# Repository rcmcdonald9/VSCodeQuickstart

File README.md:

# Pip: a 3D-printed AI robot dog, designed to be easy to assemble

A small four-legged robot dog (about 25 cm long, ~1.9 kg) that you print on a **Bambu Lab P2S** and run on a **Raspberry Pi 5**.

- **Moving head:** pans and tilts, with a camera, distance sensor, speaker and mic.
- **Voice:** listens for commands offline and talks back.
- **AI:** hands harder requests to **Claude**, which plans multi-step tasks with the dog's tools and camera.

**v2 is designed so that every step is a straight-down move**, with one screw type and automatic calibration. A person with a screwdriver assembles it quickly, and a cheap machine could do it later. Every change is checked in a **physics simulation** before printing.

## What's here

| Path | What |
|---|---|
| [`cad/`](cad) | Parametric OpenSCAD design: `params.scad`, `lib.scad`, `assembly.scad`. [`cad/stl/`](cad/stl) has print-ready STLs (no supports, no inserts) plus the leg jig. |
| [`software/`](software) | Python stack: kinematics, trot gait, bus-servo driver, head, vision, navigation, voice, Claude brain, calibration. 57 tests. |
| [`sim/`](sim) | MuJoCo simulation built from the CAD and driven by the real controller. Results and video in [`sim/results/`](sim/results). |
| [`docs/ASSEMBLY_FIRST_DESIGN.md`](docs/ASSEMBLY_FIRST_DESIGN.md) | Why it's built this way: precedent, design rules, the cheap assembly-tool ladder |
| [`docs/SIMULATION.md`](docs/SIMULATION.md) | What the sim found and what changed because of it |
| [`docs/BOM.md`](docs/BOM.md) · [`PRINTING.md`](docs/PRINTING.md) · [`WIRING.md`](docs/WIRING.md) · [`ASSEMBLY.md`](docs/ASSEMBLY.md) · [`SOFTWARE.md`](docs/SOFTWARE.md) | Build guides |

## How the design makes assembly easy

- **4 identical leg modules.** The left side uses the same module turned 180°. Each is built straight down in a printed jig, then drops into a tray socket.
- **Smart bus servos (Feetech STS3215).** They're daisy-chained, and their encoders give **automatic calibration**: the jig holds the leg straight, and one command records the zeros.
- **One standard servo cup and one cap** hold all 10 servos.
- **One fastener: M3 × 8.** No heat-set inserts.
- **Each part is held by the next one.** The deck traps the legs. The head drops onto a keyed hub.
- **Chamfered lead-ins** on every mating edge, and **grip lugs** with a datum notch on the main parts.

## Simulation highlights ([details](docs/SIMULATION.md))

Using the real control code against a model built from the CAD:

- Walks at **100–200 mm/s within 2 %** of the commanded speed, with **≤ 2° roll**.
- Turns in place at **45°/s**, backs up, holds every pose, and moves the head while walking. **No falls** in the 53 s test.
- Things the sim caught and fixed before any printing:
  - a wobbly gait
  - a robot that couldn't turn
  - a fall on a walking turn
  - a forward creep
  - a stop bug
  - a knee/tray collision limit
- **Warning:** the knee servos run close to their continuous torque rating while walking. Expect warm servos on long walks.

## The plan

1. **Order parts** ([BOM.md](docs/BOM.md)). The servos are half the cost. Buy the **12 V** STS3215.
2. **While you wait:** run the sim (`pip install -e "software[sim]" && python sim/run_sim.py --quick`) and the software (`python -m robodog --sim --local`).
3. **Print the test-fit pair** ([PRINTING.md §1](docs/PRINTING.md)), then the rest: about 27 h, two 1 kg spools of PETG.
4. **Set servo IDs, build the legs in the jig, calibrate, stack the body** ([ASSEMBLY.md](docs/ASSEMBLY.md)).
5. **First walk** with typed commands, then calibrate drift and turning on your floor, then turn on voice and Claude.

## Specs

| | |
|---|---|
| Degrees of freedom | 8 legs (hip pitch + knee) + 2 head (pan, tilt) |
| Actuators | 10 × Feetech STS3215 12 V bus servos (30 kg·cm stall) |
| Legs | 100 mm + 100 mm, 170 mm standing hip height |
| Compute | Raspberry Pi 5 (8 GB) |
| Sensors | Camera Module 3, VL53L1X time-of-flight (both in the head) |
| Voice | Vosk (offline speech-to-text) + Piper (offline text-to-speech), wake word "Hey Pip" |
| AI | Claude via the Anthropic API (tool use + vision), with an offline keyword fallback |
| Power | 3S2P Li-ion pack with BMS → servos directly, 5 V buck → Pi. Sim estimate: about 1–2 h. |

v1 (12 PWM servos with hip roll) is in the git history at commit `9178ef9`.

MIT licensed.

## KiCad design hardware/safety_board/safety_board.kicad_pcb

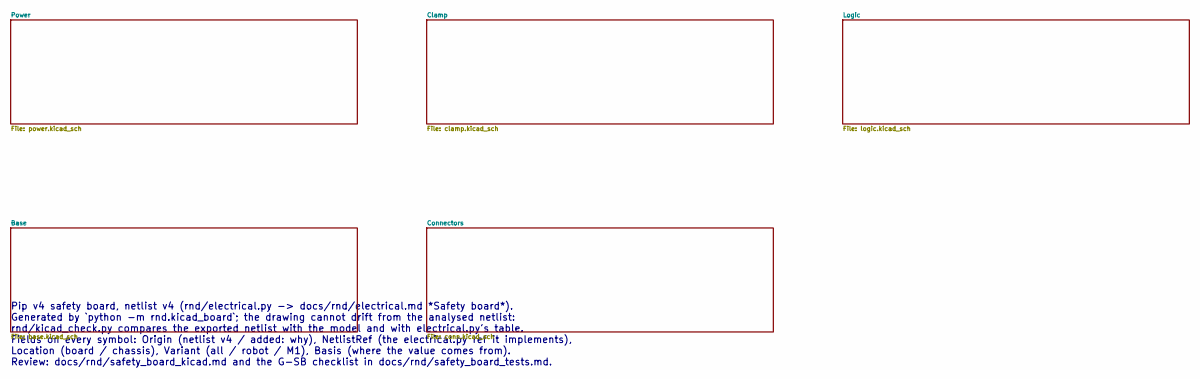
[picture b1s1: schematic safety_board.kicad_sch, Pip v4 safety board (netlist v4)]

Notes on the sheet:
Pip v4 safety board, netlist v4 (rnd/electrical.py -> docs/rnd/electrical.md *Safety board*). Generated by `python -m rnd.kicad_board`; the drawing cannot drift from the analysed netlist: rnd/kicad_check.py compares the exported netlist with the model and with electrical.py's table. Fields on every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

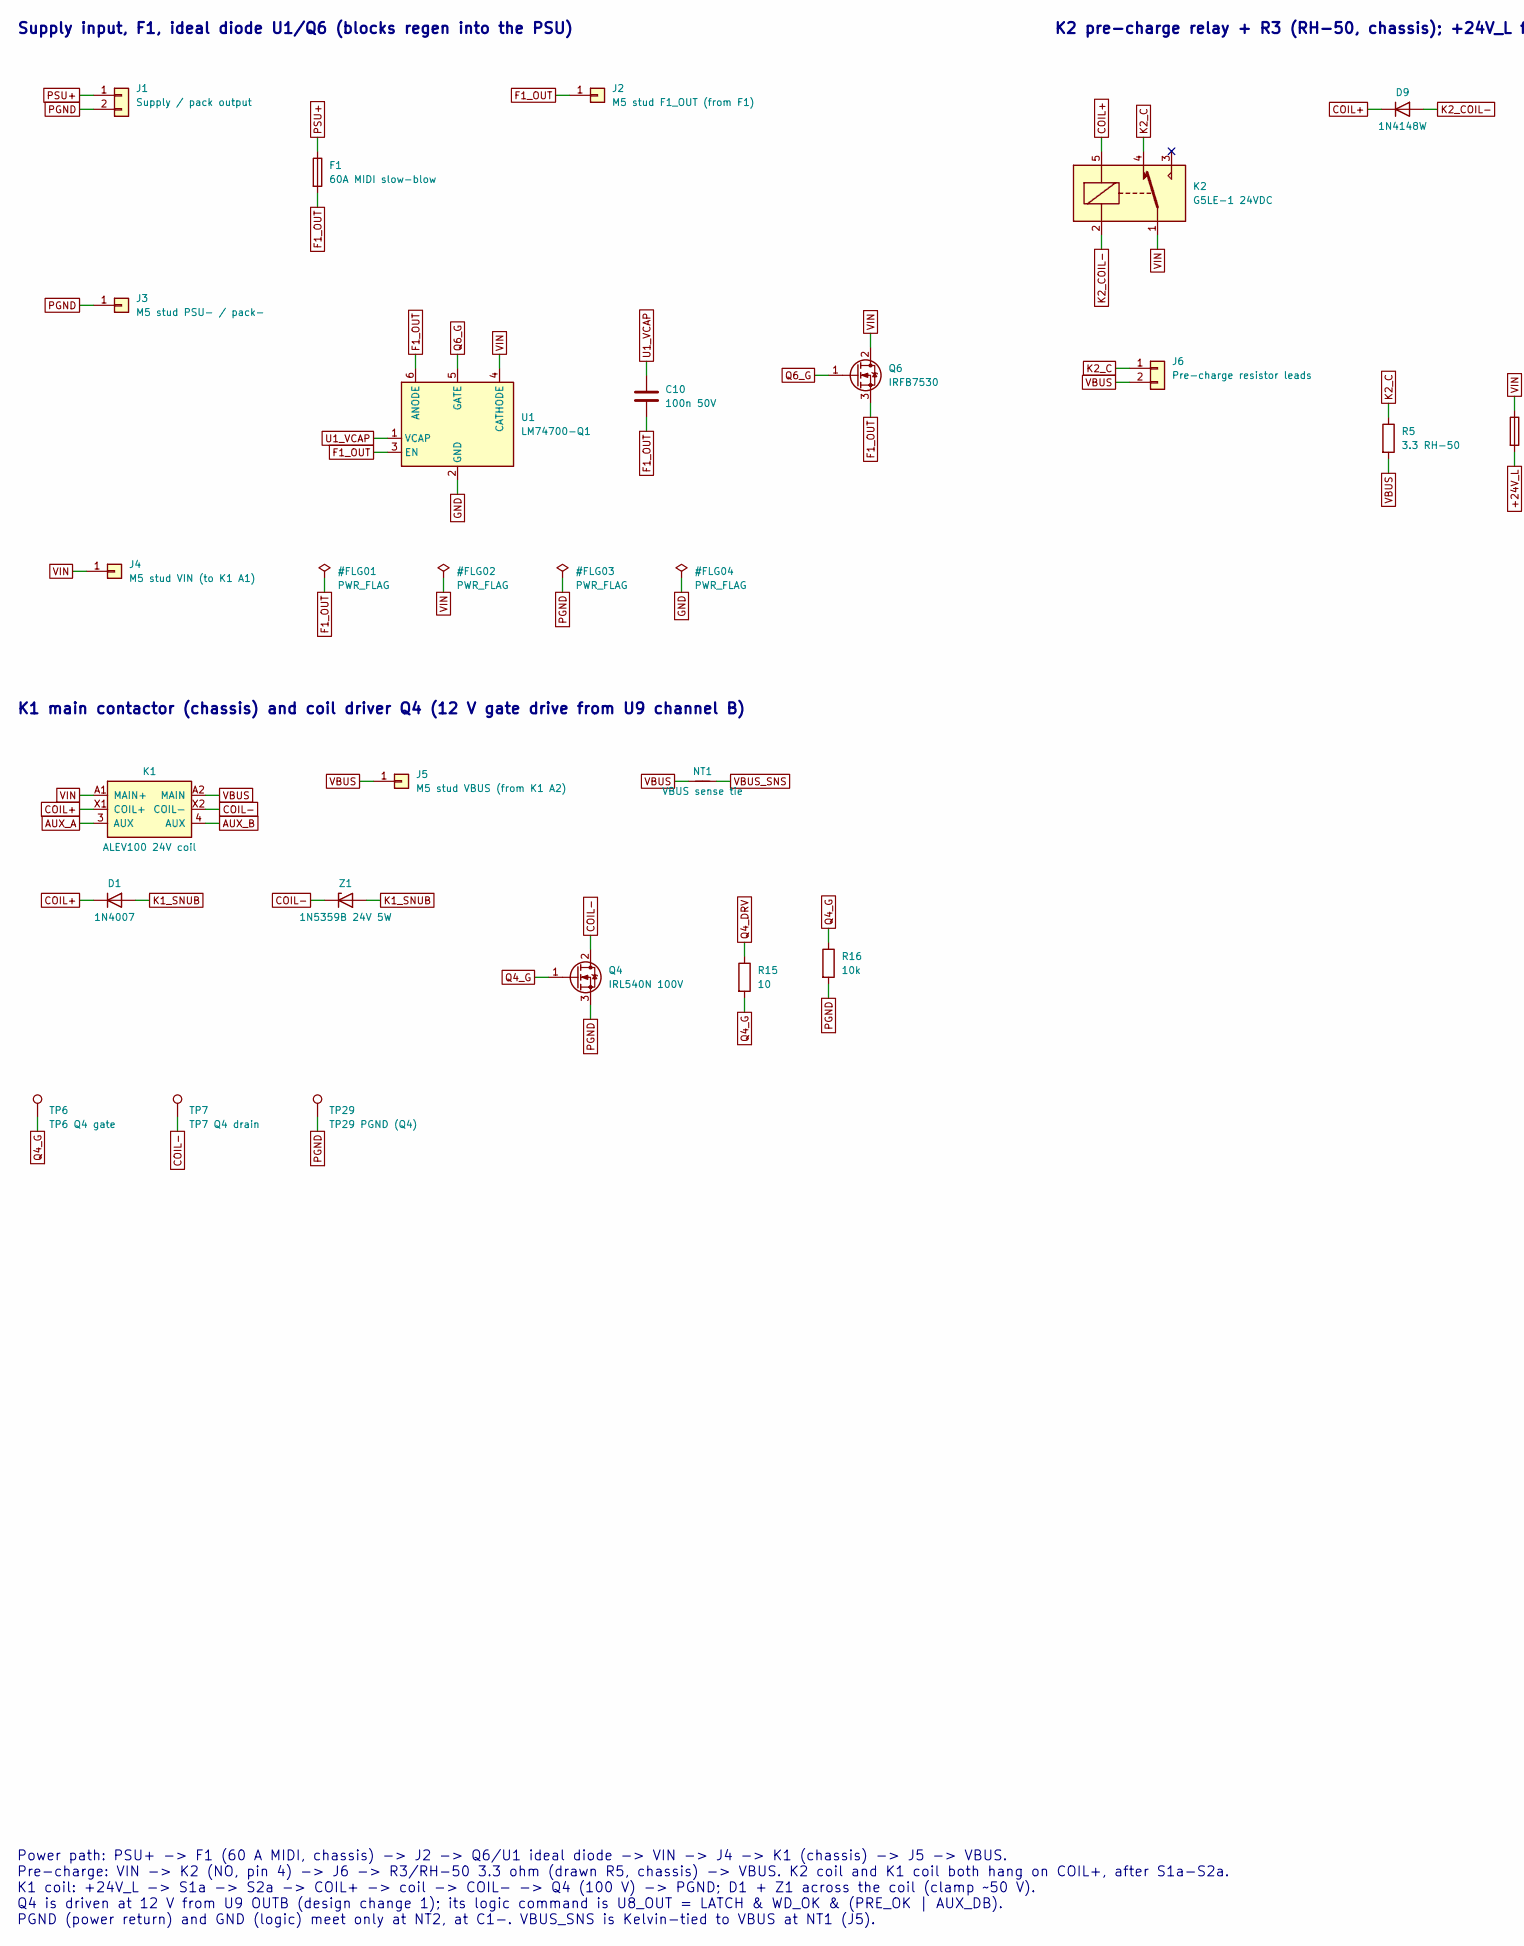
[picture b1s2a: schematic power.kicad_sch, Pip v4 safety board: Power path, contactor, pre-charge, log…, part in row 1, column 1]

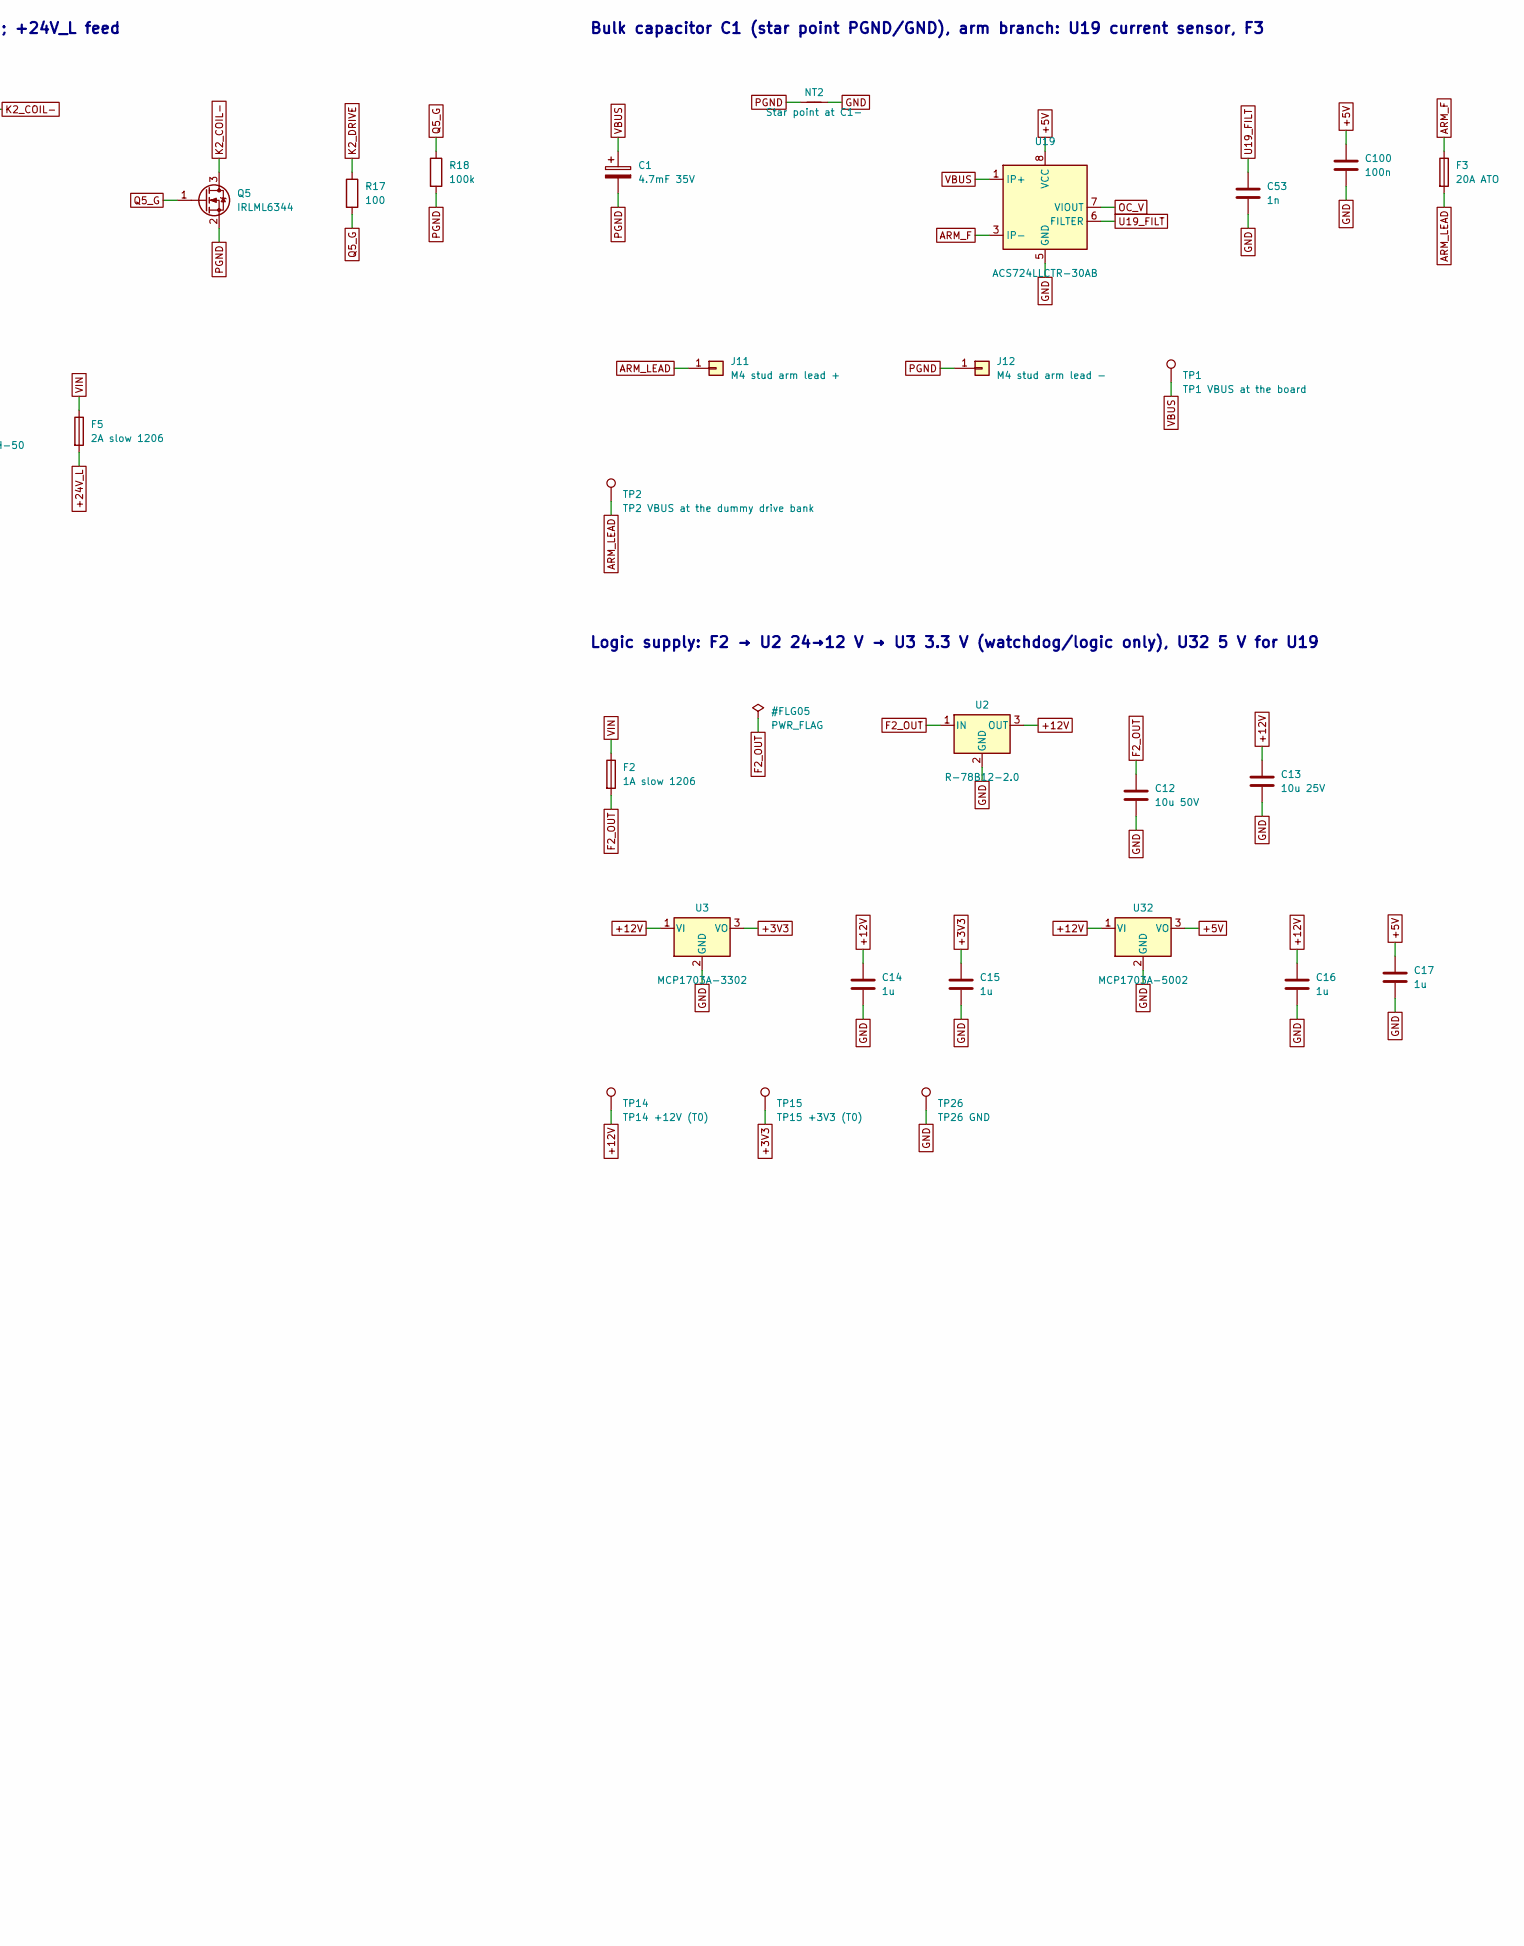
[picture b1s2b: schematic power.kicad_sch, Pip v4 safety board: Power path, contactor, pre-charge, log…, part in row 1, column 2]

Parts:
C1: 4.7mF 35V; CP_Radial_D30.0mm_P10.00mm_SnapIn
C10: 100n 50V; C_0603_1608Metric
C12: 10u 50V; C_1210_3225Metric
C13: 10u 25V; C_1210_3225Metric
C14, C15, C16, C17: 1u; C_0603_1608Metric
C53: 1n; C_0603_1608Metric
C100: 100n; C_0603_1608Metric
D1: 1N4007; D_DO-41_SOD81_P10.16mm_Horizontal
D9: 1N4148W; D_SOD-123
F1: 60A MIDI slow-blow
F2: 1A slow 1206; Fuse_1206_3216Metric
F3: 20A ATO; Fuseholder_Blade_ATO_Littelfuse_Pudenz_2_Pin
F5: 2A slow 1206; Fuse_1206_3216Metric
J1: Supply / pack output
J2: M5 stud F1_OUT (from F1); MountingHole_5.3mm_M5_Pad_Via
J3: M5 stud PSU- / pack-; MountingHole_5.3mm_M5_Pad_Via
J4: M5 stud VIN (to K1 A1); MountingHole_5.3mm_M5_Pad_Via
J5: M5 stud VBUS (from K1 A2); MountingHole_5.3mm_M5_Pad_Via
J6: Pre-charge resistor leads; TerminalBlock_Phoenix_MKDS-1,5-2-5.08_1x02_P5.08mm_Horizont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
J11: M4 stud arm lead +; MountingHole_4.3mm_M4_Pad_Via
J12: M4 stud arm lead -; MountingHole_4.3mm_M4_Pad_Via
K1: ALEV100 24V coil
K2: G5LE-1 24VDC; Relay_SPDT_Omron-G5LE-1
NT1: VBUS sense tie; NetTie-2_SMD_Pad0.5mm
NT2: Star point at C1-; NetTie-2_SMD_Pad2.0mm
Q4: IRL540N 100V; TO-220-3_Vertical
Q5: IRLML6344; SOT-23
Q6: IRFB7530; TO-220-3_Vertical
R5: 3.3 RH-50
R15: 10; R_0603_1608Metric
R16: 10k; R_0603_1608Metric
R17: 100; R_0603_1608Metric
R18: 100k; R_0603_1608Metric
TP1: TP1 VBUS at the board; TestPoint_Keystone_5005-5009_Compact
TP2: TP2 VBUS at the dummy drive bank
TP6: TP6 Q4 gate; TestPoint_Keystone_5005-5009_Compact
TP7: TP7 Q4 drain; TestPoint_Keystone_5005-5009_Compact
TP14: TP14 +12V (T0); TestPoint_Keystone_5005-5009_Compact
TP15: TP15 +3V3 (T0); TestPoint_Keystone_5005-5009_Compact
TP26: TP26 GND; TestPoint_Keystone_5005-5009_Compact
TP29: TP29 PGND (Q4); TestPoint_Keystone_5005-5009_Compact
U1: LM74700-Q1; SOT-23-6
U2: R-78B12-2.0; Converter_DCDC_RECOM_R-78B-2.0_THT
U3: MCP1703A-3302; SOT-223-3_TabPin2
U19: ACS724LLCTR-30AB; SOIC-8_3.9x4.9mm_P1.27mm
U32: MCP1703A-5002; SOT-223-3_TabPin2
Z1: 1N5359B 24V 5W; D_DO-201AE_P15.24mm_Horizontal

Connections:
+3V3: C15.1, TP15.1, U3.3 (VO); also elsewhere on the board
+5V: C17.1, C100.1, U19.8 (VCC), U32.3 (VO)
+12V: C13.1, C14.1, C16.1, TP14.1, U2.3 (OUT), U3.1 (VI), U32.1 (VI); also elsewhere on the board
+24V_L: F5.2; also elsewhere on the board
ARM_F: F3.1, U19.3 (IP-), U19.4 (IP-)
ARM_LEAD: F3.2, J11.1, TP2.1
COIL+: D1.1 (K), D9.1 (K), K1.X1 (COIL+), K2.5; also elsewhere on the board
COIL-: K1.X2 (COIL-), Q4.2 (D), TP7.1, Z1.1 (K); also elsewhere on the board
F1_OUT: C10.2, F1.2, J2.1, Q6.3 (S), U1.3 (EN), U1.6 (ANODE)
F2_OUT: C12.1, F2.2, U2.1 (IN)
GND: C12.2, C13.2, C14.2, C15.2, C16.2, C17.2, C53.2, C100.2, NT2.2, TP26.1, U1.2 (GND), U2.2 (GND), U3.2 (GND), U19.5 (GND), U32.2 (GND); also elsewhere on the board
K1_SNUB: D1.2 (A), Z1.2 (A)
K2_C: J6.1, K2.4, R5.1
K2_COIL-: D9.2 (A), K2.2, Q5.3 (D)
K2_DRIVE: R17.1; also elsewhere on the board
unnamed: F1.1, J1.1
OC_V: U19.7 (VIOUT); also elsewhere on the board
PGND: C1.2, J1.2, J3.1, J12.1, NT2.1, Q4.3 (S), Q5.2 (S), R16.2, R18.2, TP29.1; also elsewhere on the board
Q4_DRV: R15.1; also elsewhere on the board
Q4_G: Q4.1 (G), R15.2, R16.1, TP6.1
Q5_G: Q5.1 (G), R17.2, R18.1
Q6_G: Q6.1 (G), U1.5 (GATE)
U1_VCAP: C10.1, U1.1 (VCAP)
U19_FILT: C53.1, U19.6 (FILTER)
VBUS: C1.1, J5.1, J6.2, K1.A2 (MAIN), NT1.1, R5.2, TP1.1, U19.1 (IP+), U19.2 (IP+); also elsewhere on the board
VBUS_SNS: NT1.2; also elsewhere on the board
VIN: F2.1, F5.1, J4.1, K1.A1 (MAIN+), K2.1, Q6.2 (D), U1.4 (CATHODE); also elsewhere on the board

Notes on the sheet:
Supply input, F1, ideal diode U1/Q6 (blocks regen into the PSU)
K1 main contactor (chassis) and coil driver Q4 (12 V gate drive from U9 channel B)
K2 pre-charge relay + R3 (RH-50, chassis); +24V_L feed
Bulk capacitor C1 (star point PGND/GND), arm branch: U19 current sensor, F3
Logic supply: F2 → U2 24→12 V → U3 3.3 V (watchdog/logic only), U32 5 V for U19
Power path: PSU+ -> F1 (60 A MIDI, chassis) -> J2 -> Q6/U1 ideal diode -> VIN -> J4 -> K1 (chassis) -> J5 -> VBUS. Pre-charge: VIN -> K2 (NO, pin 4) -> J6 -> R3/RH-50 3.3 ohm (drawn R5, chassis) -> VBUS. K2 coil and K1 coil both hang on COIL+, after S1a-S2a. K1 coil: +24V_L -> S1a -> S2a -> COIL+ -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

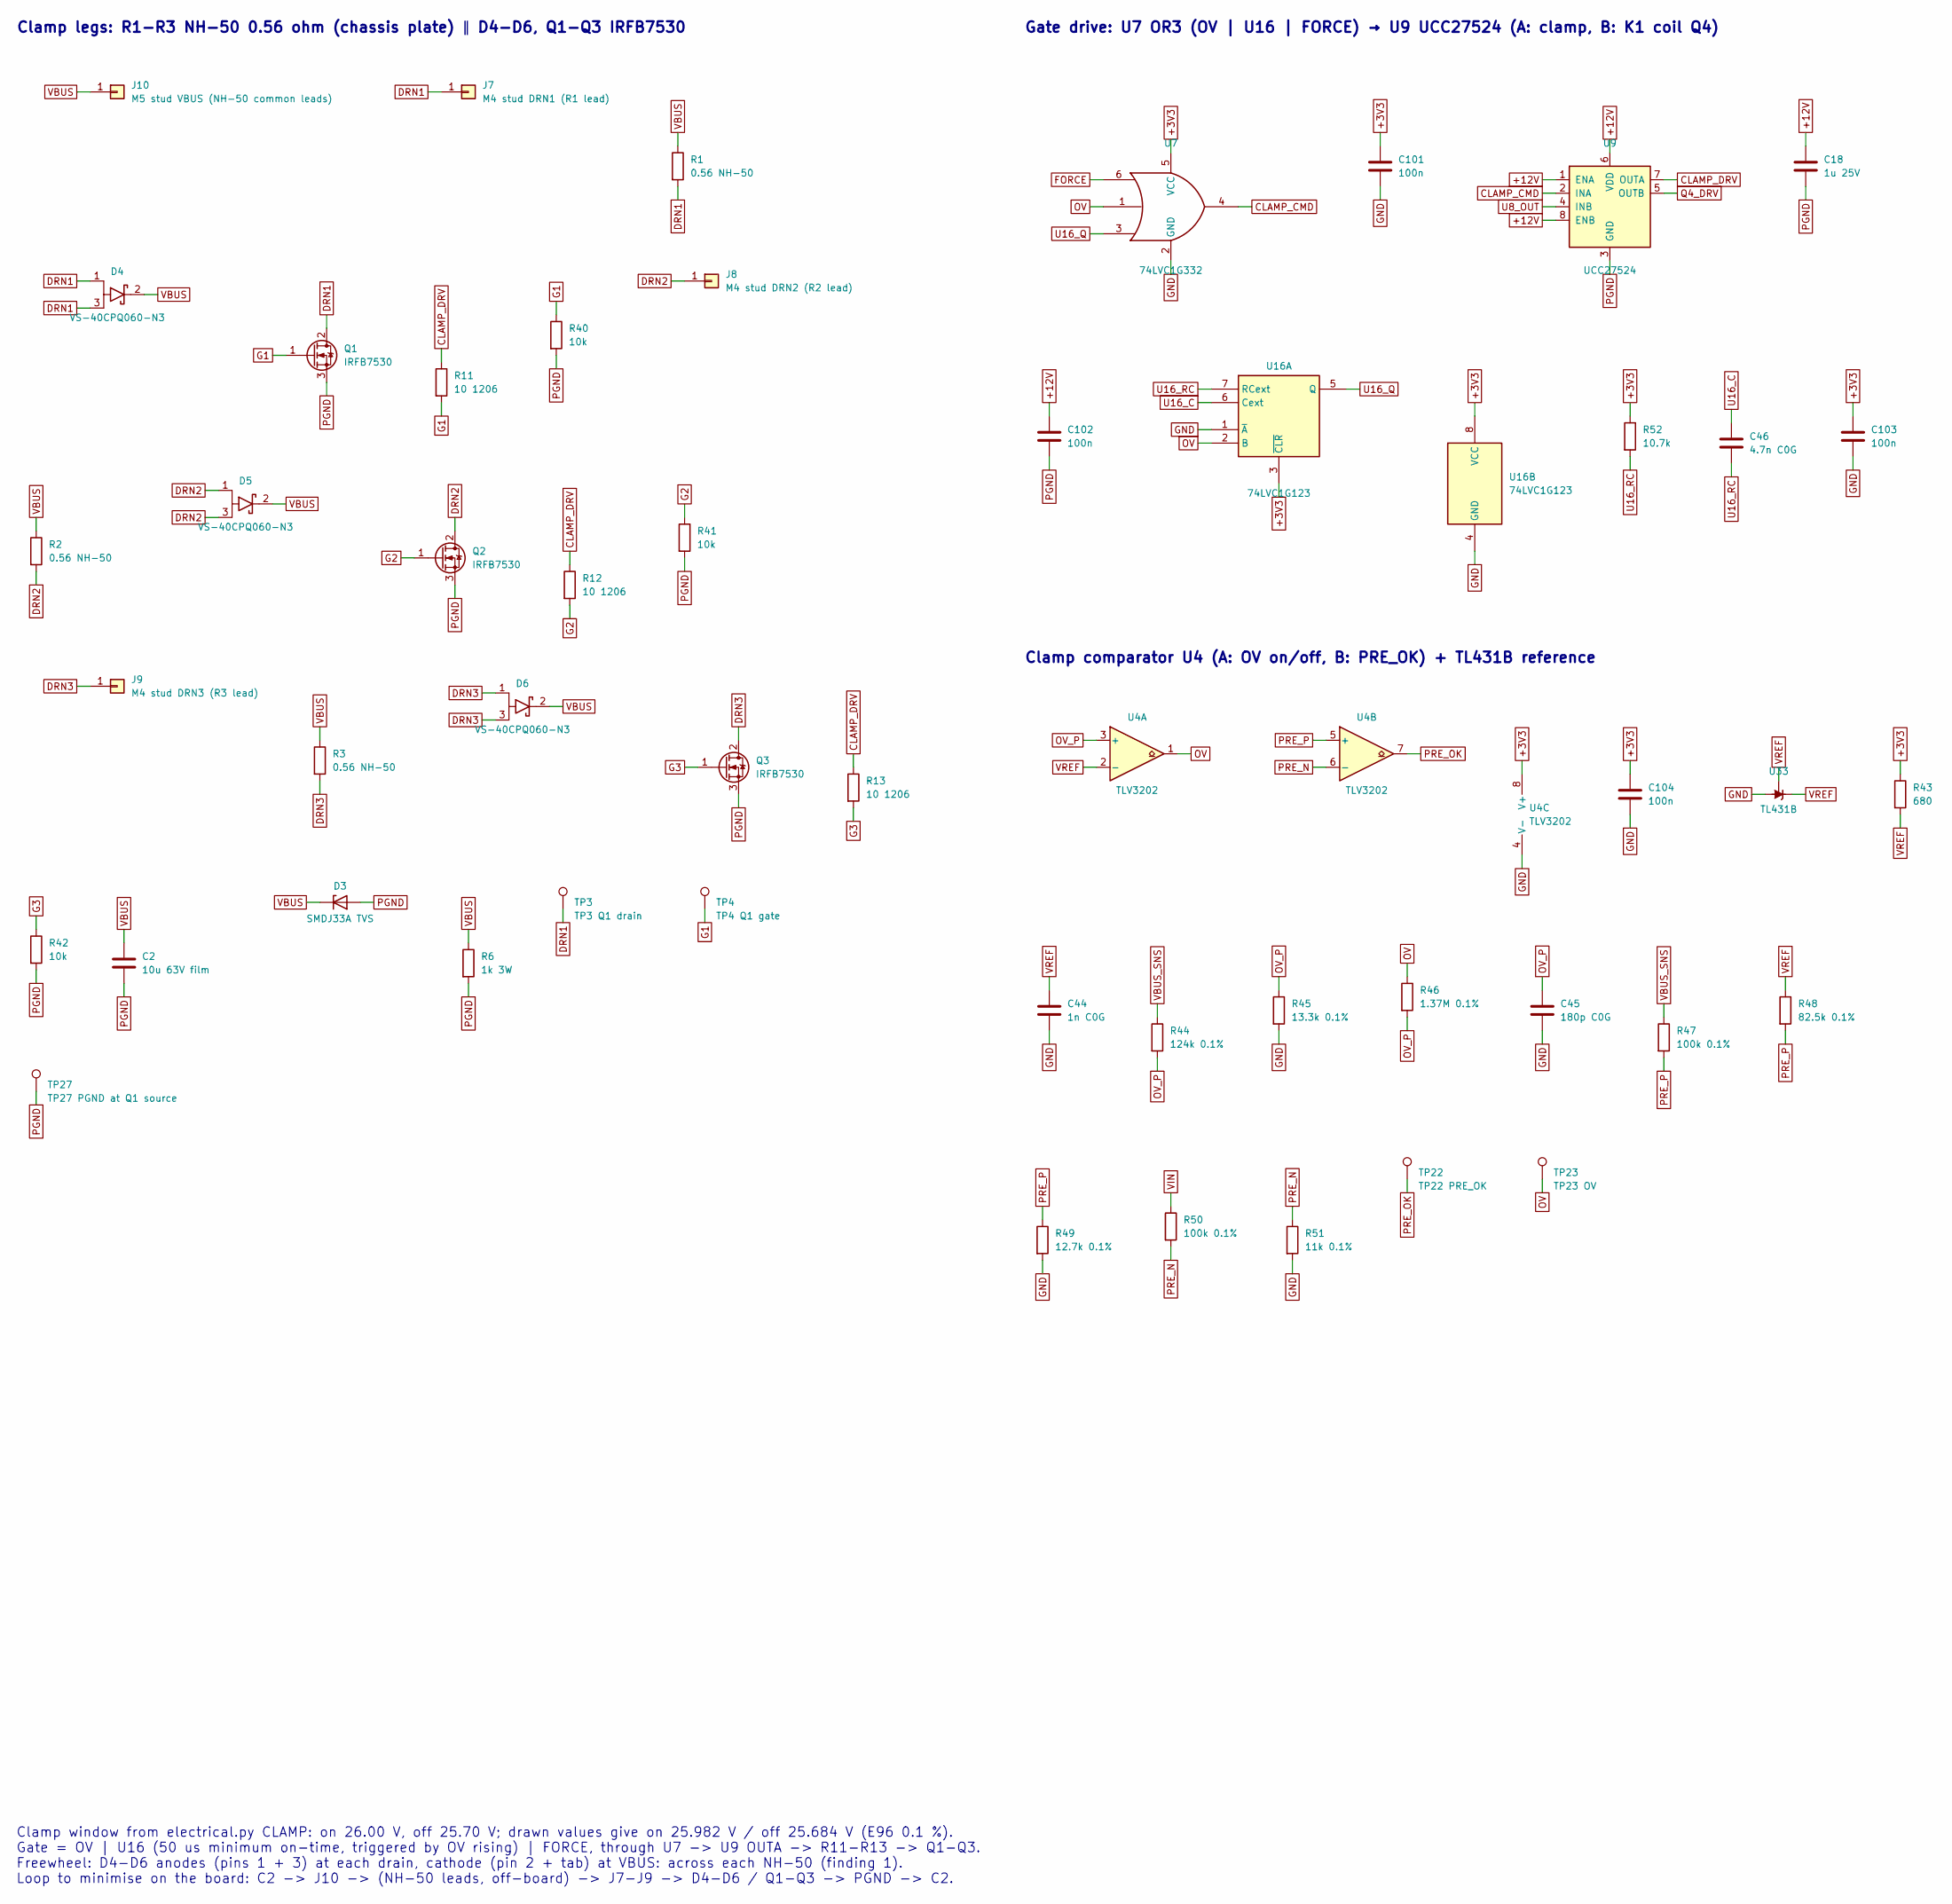
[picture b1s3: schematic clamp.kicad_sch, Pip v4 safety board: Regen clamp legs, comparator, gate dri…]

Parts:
C2: 10u 63V film; C_Rect_L31.5mm_W11.0mm_P27.50mm_MKS4
C18: 1u 25V; C_1206_3216Metric
C44: 1n C0G; C_0603_1608Metric
C45: 180p C0G; C_0603_1608Metric
C46: 4.7n C0G; C_0603_1608Metric
C101, C102, C103, C104: 100n; C_0603_1608Metric
D3: SMDJ33A TVS; D_SMC
D4, D5, D6: VS-40CPQ060-N3; TO-247-3_Vertical
J7: M4 stud DRN1 (R1 lead); MountingHole_4.3mm_M4_Pad_Via
J8: M4 stud DRN2 (R2 lead); MountingHole_4.3mm_M4_Pad_Via
J9: M4 stud DRN3 (R3 lead); MountingHole_4.3mm_M4_Pad_Via
J10: M5 stud VBUS (NH-50 common leads); MountingHole_5.3mm_M5_Pad_Via
Q1, Q2, Q3: IRFB7530; TO-220-3_Vertical
R1, R2, R3: 0.56 NH-50
R6: 1k 3W; R_Axial_Power_L20.0mm_W6.4mm_P22.40mm
R11, R12, R13: 10 1206; R_1206_3216Metric
R40, R41, R42: 10k; R_0603_1608Metric
R43: 680; R_0603_1608Metric
R44: 124k 0.1%; R_0603_1608Metric
R45: 13.3k 0.1%; R_0603_1608Metric
R46: 1.37M 0.1%; R_0603_1608Metric
R47, R50: 100k 0.1%; R_0603_1608Metric
R48: 82.5k 0.1%; R_0603_1608Metric
R49: 12.7k 0.1%; R_0603_1608Metric
R51: 11k 0.1%; R_0603_1608Metric
R52: 10.7k; R_0603_1608Metric
TP3: TP3 Q1 drain; TestPoint_Keystone_5005-5009_Compact
TP4: TP4 Q1 gate; TestPoint_Keystone_5005-5009_Compact
TP22: TP22 PRE_OK; TestPoint_Keystone_5005-5009_Compact
TP23: TP23 OV; TestPoint_Keystone_5005-5009_Compact
TP27: TP27 PGND at Q1 source; TestPoint_Keystone_5005-5009_Compact
U4: TLV3202; SOIC-8_3.9x4.9mm_P1.27mm
U7: 74LVC1G332; SOT-23-6
U9: UCC27524; SOIC-8_3.9x4.9mm_P1.27mm
U16: 74LVC1G123; VSSOP-8_2.3x2mm_P0.5mm
U33: TL431B; SOT-23

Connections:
+3V3: C101.1, C103.1, C104.1, R43.1, R52.1, U4.8 (V+), U7.5 (VCC), U16.3 (~CLR), U16.8 (VCC); also elsewhere on the board
+12V: C18.1, C102.1, U9.1 (ENA), U9.6 (VDD), U9.8 (ENB); also elsewhere on the board
CLAMP_CMD: U7.4, U9.2 (INA)
CLAMP_DRV: R11.1, R12.1, R13.1, U9.7 (OUTA)
DRN1: D4.1 (A), D4.3 (A), J7.1, Q1.2 (D), R1.2, TP3.1
DRN2: D5.1 (A), D5.3 (A), J8.1, Q2.2 (D), R2.2
DRN3: D6.1 (A), D6.3 (A), J9.1, Q3.2 (D), R3.2
FORCE: U7.6; also elsewhere on the board
G1: Q1.1 (G), R11.2, R40.1, TP4.1
G2: Q2.1 (G), R12.2, R41.1
G3: Q3.1 (G), R13.2, R42.1
GND: C44.2, C45.2, C101.2, C103.2, C104.2, R45.2, R49.2, R51.2, U4.4 (V-), U7.2 (GND), U16.1 (~A), U16.4 (GND), U33.3 (A); also elsewhere on the board
OV: R46.1, TP23.1, U4.1, U7.1, U16.2 (B)
OV_P: C45.1, R44.2, R45.1, R46.2, U4.3 (+)
PGND: C2.2, C18.2, C102.2, D3.2 (A), Q1.3 (S), Q2.3 (S), Q3.3 (S), R6.2, R40.2, R41.2, R42.2, TP27.1, U9.3 (GND); also elsewhere on the board
PRE_N: R50.2, R51.1, U4.6 (-)
PRE_OK: TP22.1, U4.7; also elsewhere on the board
PRE_P: R47.2, R48.2, R49.1, U4.5 (+)
Q4_DRV: U9.5 (OUTB); also elsewhere on the board
U8_OUT: U9.4 (INB); also elsewhere on the board
U16_C: C46.1, U16.6 (Cext)
U16_Q: U7.3, U16.5 (Q)
U16_RC: C46.2, R52.2, U16.7 (RCext)
VBUS: C2.1, D3.1 (K), D4.2 (K), D5.2 (K), D6.2 (K), J10.1, R1.1, R2.1, R3.1, R6.1; also elsewhere on the board
VBUS_SNS: R44.1, R47.1; also elsewhere on the board
VIN: R50.1; also elsewhere on the board
VREF: C44.1, R43.2, R48.1, U4.2 (-), U33.1 (K), U33.2 (REF); also elsewhere on the board

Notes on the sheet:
Clamp legs: R1-R3 NH-50 0.56 ohm (chassis plate) ∥ D4-D6, Q1-Q3 IRFB7530
Gate drive: U7 OR3 (OV | U16 | FORCE) → U9 UCC27524 (A: clamp, B: K1 coil Q4)
Clamp comparator U4 (A: OV on/off, B: PRE_OK) + TL431B reference
Clamp window from electrical.py CLAMP: on 26.00 V, off 25.70 V; drawn values give on 25.982 V / off 25.684 V (E96 0.1 %). Gate = OV | U16 (50 us minimum on-time, triggered by OV rising) | FORCE, through U7 -> U9 OUTA -> R11-R13 -> Q1-Q3. Freewheel: D4-D6 anodes (pins 1 + 3) at each drain, cathode (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
